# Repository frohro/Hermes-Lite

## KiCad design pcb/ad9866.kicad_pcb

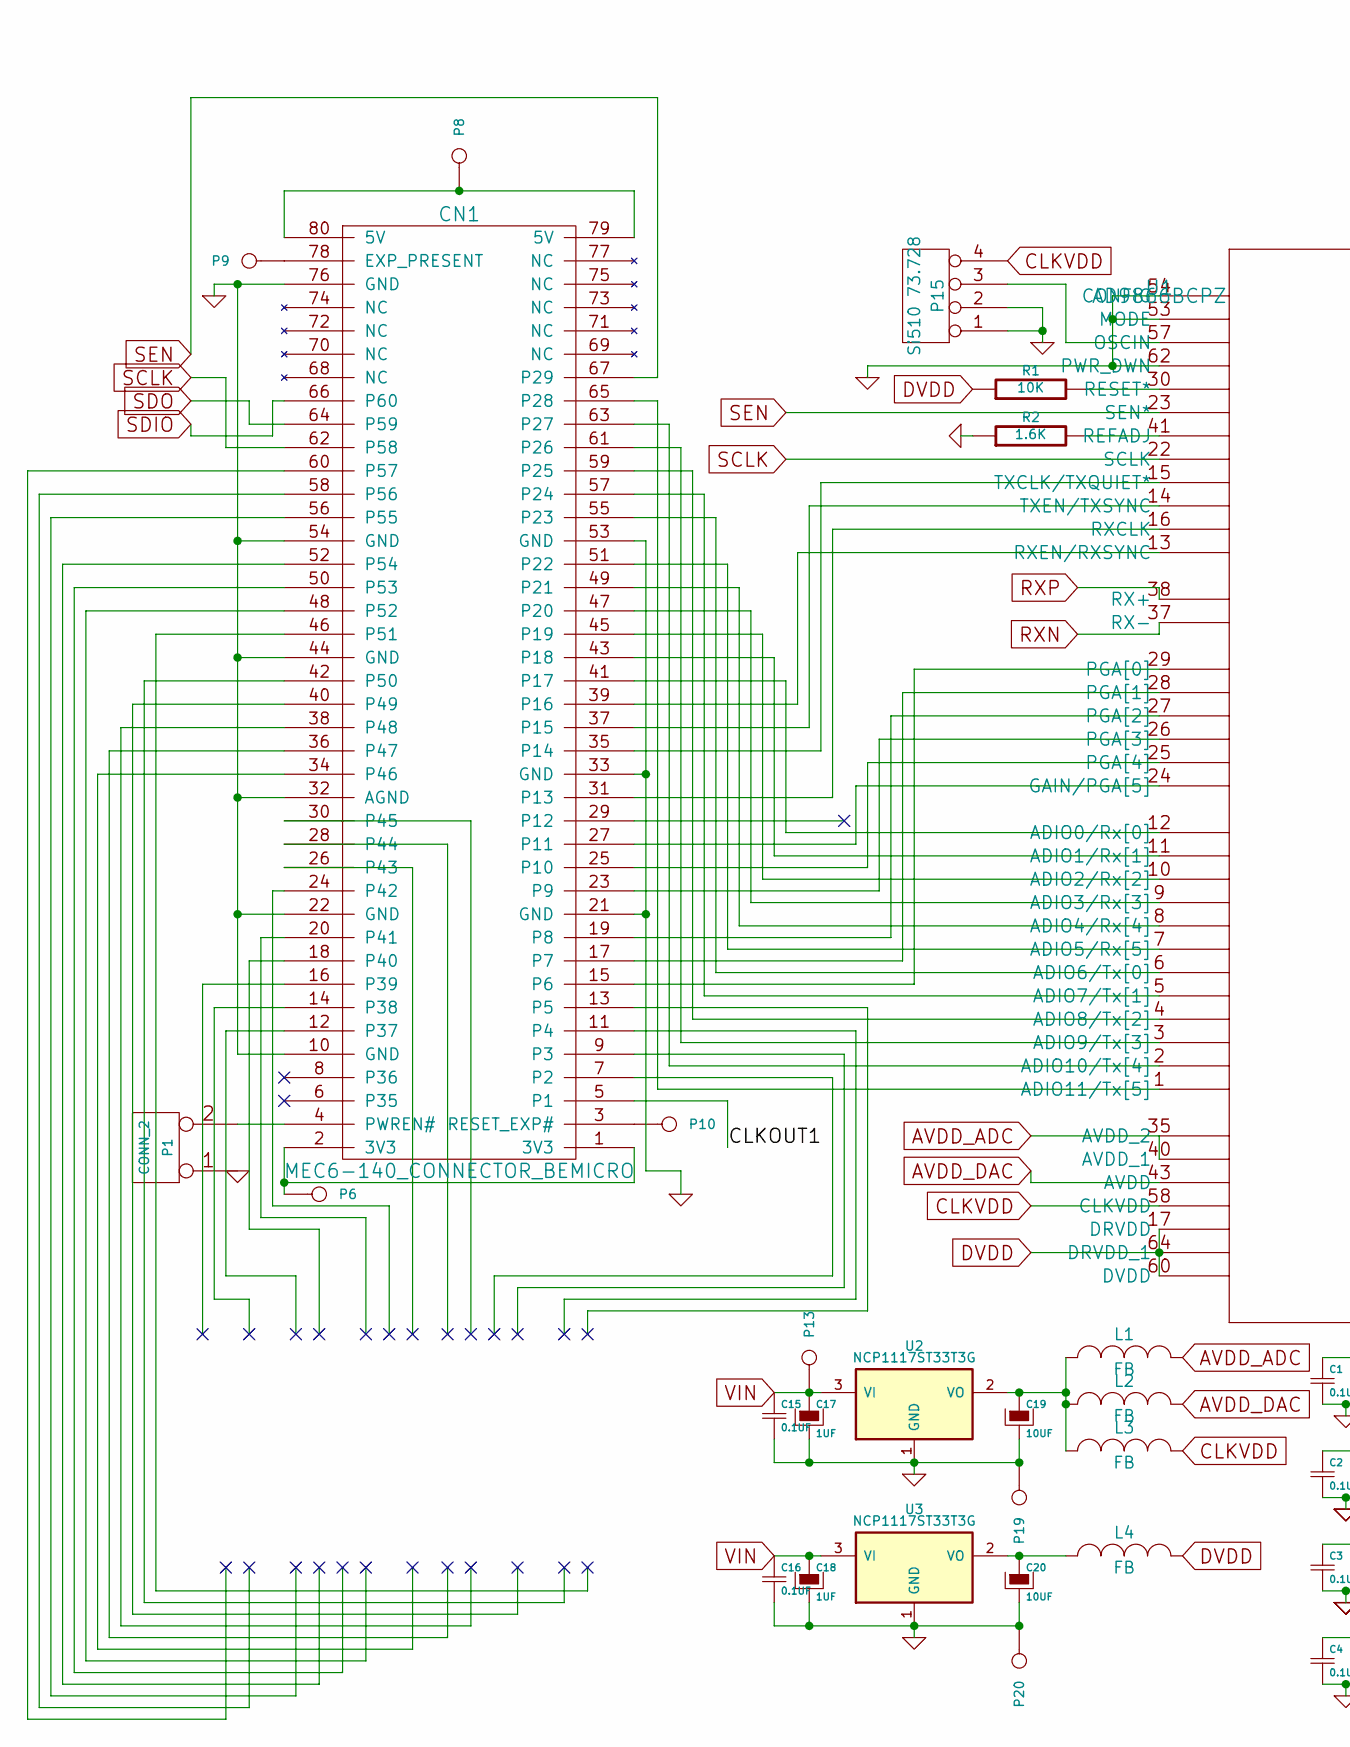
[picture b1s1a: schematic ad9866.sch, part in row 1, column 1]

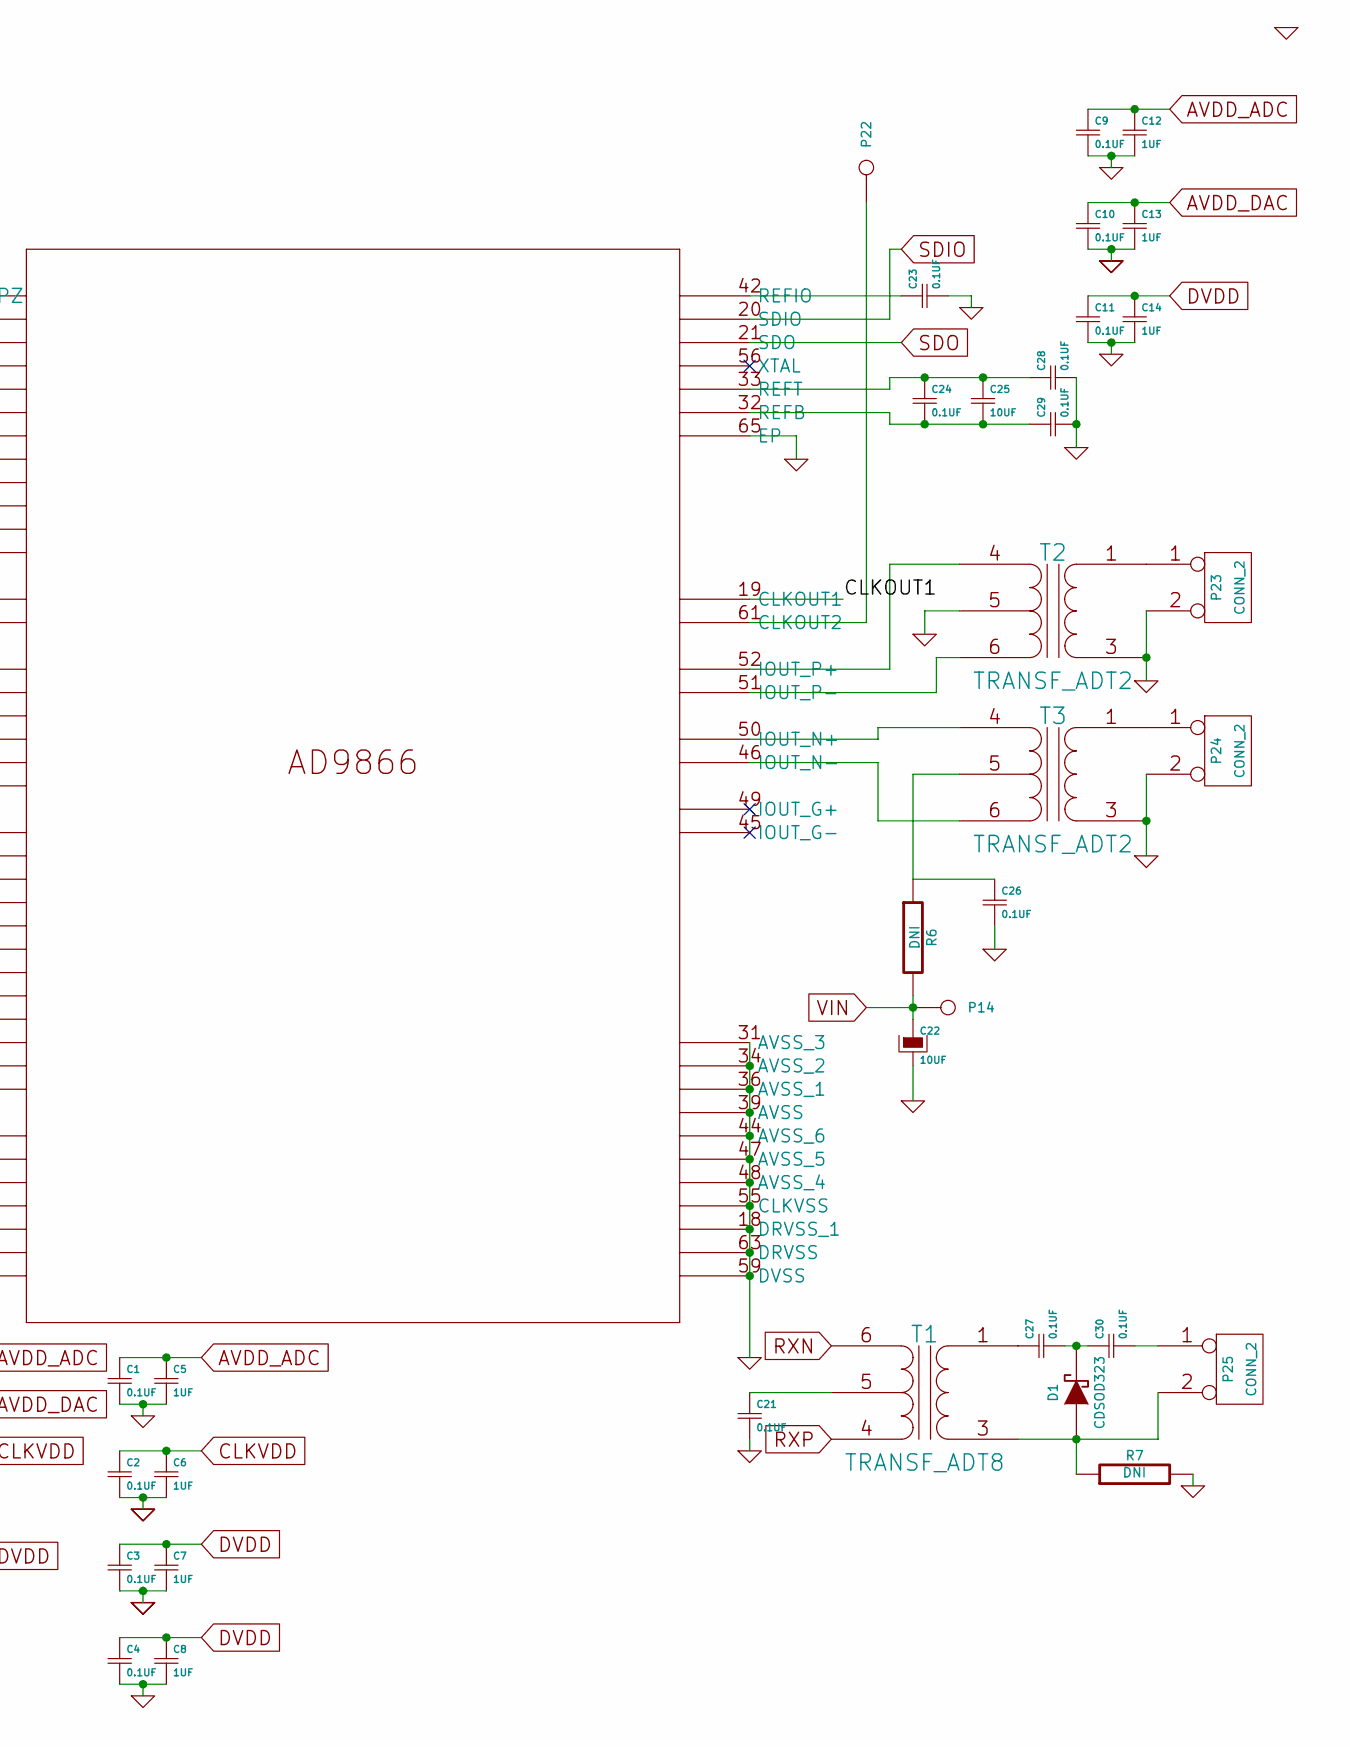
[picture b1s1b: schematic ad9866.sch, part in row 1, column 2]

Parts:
C1, C2, C3, C4, C9, C10, C11, C15, C16, C21, C23, C24, C26, C27, C28, C29, C30: 0.1UF
C5, C6, C7, C8, C12, C13, C14, C17, C18: 1UF
C19, C20, C22, C25: 10UF
CN1: MEC6-140_CONNECTOR_BEMICRO
D1: CDSOD323
L1, L2, L3, L4: FB
P1, P23, P24, P25: CONN_2
P6, P8, P9, P10, P13, P14, P19, P20, P22: CONN_1
P15: Si510 73.728
R1: 10K
R2: 1.6K
R6, R7: DNI
T1: TRANSF_ADT8
T2, T3: TRANSF_ADT2
U1: AD9866BCPZ
U2, U3: NCP1117ST33T3G

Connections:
/CLKOUT1: CN1.5 (P1), U1.19 (CLKOUT1)
AVDD_ADC: C1.1, C5.1, C9.1, C12.1, L1.2, U1.35 (AVDD_2), U1.40 (AVDD_1)
AVDD_DAC: C10.1, C13.1, L2.2, U1.43 (AVDD)
CLKVDD: C2.1, C6.1, L3.2, P15.4, U1.58 (CLKVDD)
DVDD: C3.1, C4.1, C7.1, C8.1, C11.1, C14.1, L4.2, R1.1, U1.17 (DRVDD), U1.60 (DVDD), U1.64 (DRVDD_1)
GND: C1.2, C2.2, C3.2, C4.2, C5.2, C6.2, C7.2, C8.2, C9.2, C10.2, C11.2, C12.2, C13.2, C14.2, C15.2, C16.2, C17.2, C18.2, C19.2, C20.2, C21.2, C22.2, C23.2, C26.2, C28.2, C29.2, CN1.10 (GND), CN1.21 (GND), CN1.22 (GND), CN1.32 (AGND), CN1.33 (GND), CN1.44 (GND), CN1.53 (GND), CN1.54 (GND), CN1.76 (GND), P1.1, P15.1, P15.2, P19.1, P20.1, P23.2 (PM), P24.2 (PM), R2.1, R7.2, T2.3 (S1), T2.5 (PM), T3.3 (S1), U1.18 (DRVSS_1), U1.31 (AVSS_3), U1.34 (AVSS_2), U1.36 (AVSS_1), U1.39 (AVSS), U1.44 (AVSS_6), U1.47 (AVSS_5), U1.48 (AVSS_4), U1.53 (MODE), U1.54 (CONFIG), U1.55 (CLKVSS), U1.59 (DVSS), U1.62 (PWR_DWN), U1.63 (DRVSS), U1.65 (EP), U2.1 (GND), U3.1 (GND)
unnamed: C19.1, L1.1, L2.1, L3.1, U2.2 (VO)
unnamed: C20.1, L4.1, U3.2 (VO)
unnamed: C21.1, T1.5 (PM)
unnamed: C23.1, U1.42 (REFIO)
unnamed: C24.1, C25.1, C28.1, U1.33 (REFT)
unnamed: C24.2, C25.2, C29.1, U1.32 (REFB)
unnamed: C26.1, R6.1, T3.5 (PM)
unnamed: C27.1, T1.1 (S2)
unnamed: C27.2, C30.1, D1.2 (K)
unnamed: C30.2, P25.1
unnamed: CN1.1 (3V3), CN1.2 (3V3), P6.1
unnamed: CN1.3 (RESET_EXP#), P10.1
unnamed: CN1.4 (PWREN#), P1.2 (PM)
unnamed: CN1.15 (P6), U1.29 (PGA[0])
unnamed: CN1.17 (P7), U1.28 (PGA[1])
unnamed: CN1.19 (P8), U1.27 (PGA[2])
unnamed: CN1.23 (P9), U1.26 (PGA[3])
unnamed: CN1.25 (P10), U1.25 (PGA[4])
unnamed: CN1.27 (P11), U1.24 (GAIN/PGA[5])
unnamed: CN1.31 (P13), U1.16 (RXCLK)
unnamed: CN1.35 (P14), U1.15 (TXCLK/TXQUIET*)
unnamed: CN1.37 (P15), U1.14 (TXEN/TXSYNC)
unnamed: CN1.39 (P16), U1.13 (RXEN/RXSYNC)
unnamed: CN1.41 (P17), U1.12 (ADIO0/Rx[0])
unnamed: CN1.43 (P18), U1.11 (ADIO1/Rx[1])
unnamed: CN1.45 (P19), U1.10 (ADIO2/Rx[2])
unnamed: CN1.47 (P20), U1.9 (ADIO3/Rx[3])
unnamed: CN1.49 (P21), U1.8 (ADIO4/Rx[4])
unnamed: CN1.51 (P22), U1.7 (ADIO5/Rx[5])
unnamed: CN1.55 (P23), U1.6 (ADIO6/Tx[0])
unnamed: CN1.57 (P24), U1.5 (ADIO7/Tx[1])
unnamed: CN1.59 (P25), U1.4 (ADIO8/Tx[2])
unnamed: CN1.61 (P26), U1.3 (ADIO9/Tx[3])
unnamed: CN1.63 (P27), U1.2 (ADIO10/Tx[4])
unnamed: CN1.65 (P28), U1.1 (ADIO11/Tx[5])
unnamed: CN1.78 (EXP_PRESENT), P9.1
unnamed: CN1.79 (5V), CN1.80 (5V), P8.1
unnamed: D1.1 (A), P25.2 (PM), R7.1, T1.3 (S1)
unnamed: P15.3, U1.57 (OSCIN)
unnamed: P22.1, U1.61 (CLKOUT2)
unnamed: P23.1, T2.1 (S2)
unnamed: P24.1, T3.1 (S2)
unnamed: R1.2, U1.30 (RESET*)
unnamed: R2.2, U1.41 (REFADJ)
unnamed: T2.4 (PR1), U1.52 (IOUT_P+)
unnamed: T2.6 (PR2), U1.51 (IOUT_P-)
unnamed: T3.4 (PR1), U1.50 (IOUT_N+)
unnamed: T3.6 (PR2), U1.46 (IOUT_N-)
RXN: T1.6 (PR1), U1.37 (RX-)
RXP: T1.4 (PR2), U1.38 (RX+)
SCLK: CN1.62 (P58), U1.22 (SCLK)
SDIO: CN1.66 (P60), U1.20 (SDIO)
SDO: CN1.64 (P59), U1.21 (SDO)
SEN: CN1.67 (P29), U1.23 (SEN*)
VIN: C15.1, C16.1, C17.1, C18.1, C22.1, P13.1, P14.1, R6.2, U2.3 (VI), U3.3 (VI)

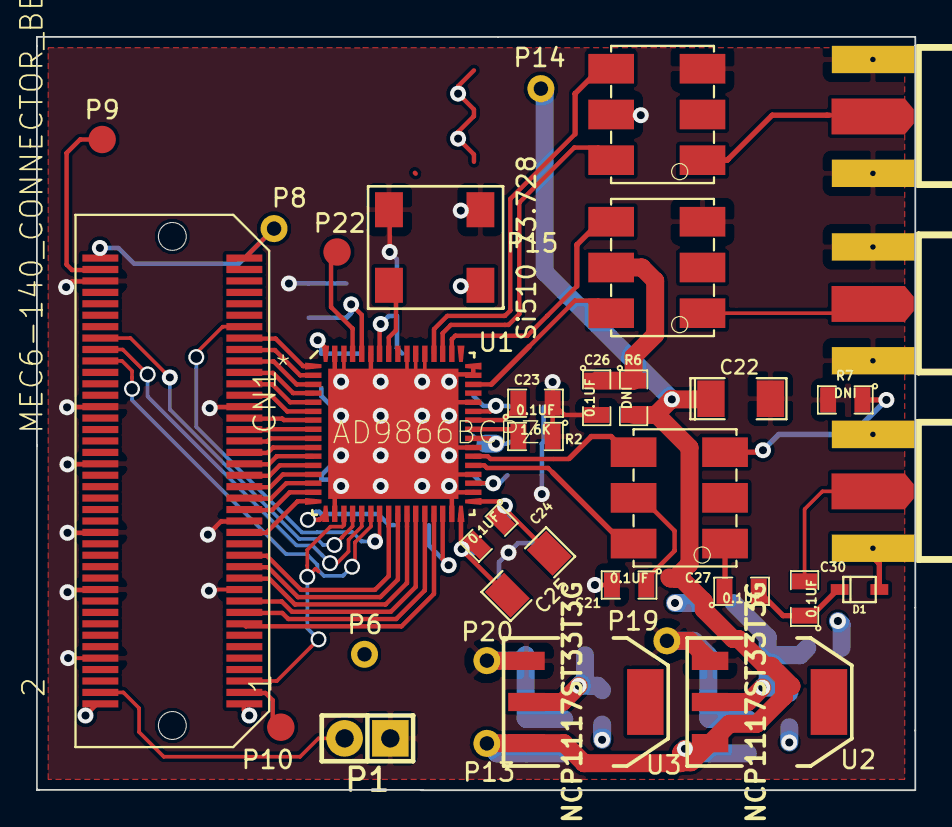
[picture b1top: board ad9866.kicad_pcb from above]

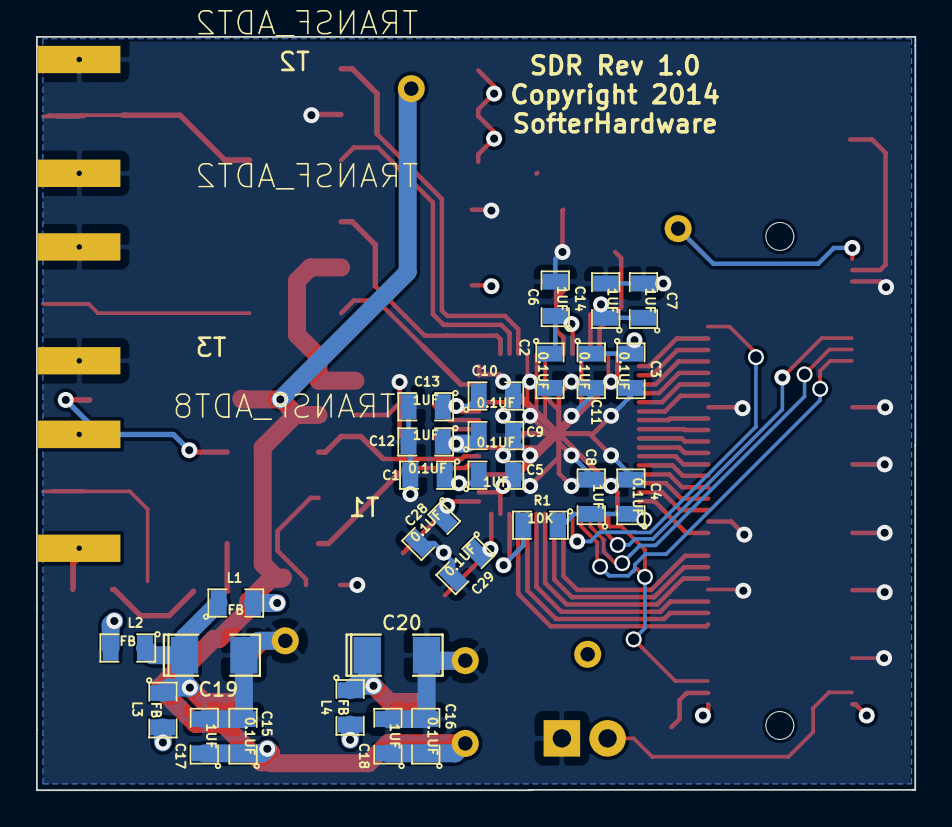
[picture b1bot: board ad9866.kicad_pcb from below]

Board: 4 copper layers, 48.8 x 41.8 mm, 60 parts (27 on the bottom side), 61 nets.

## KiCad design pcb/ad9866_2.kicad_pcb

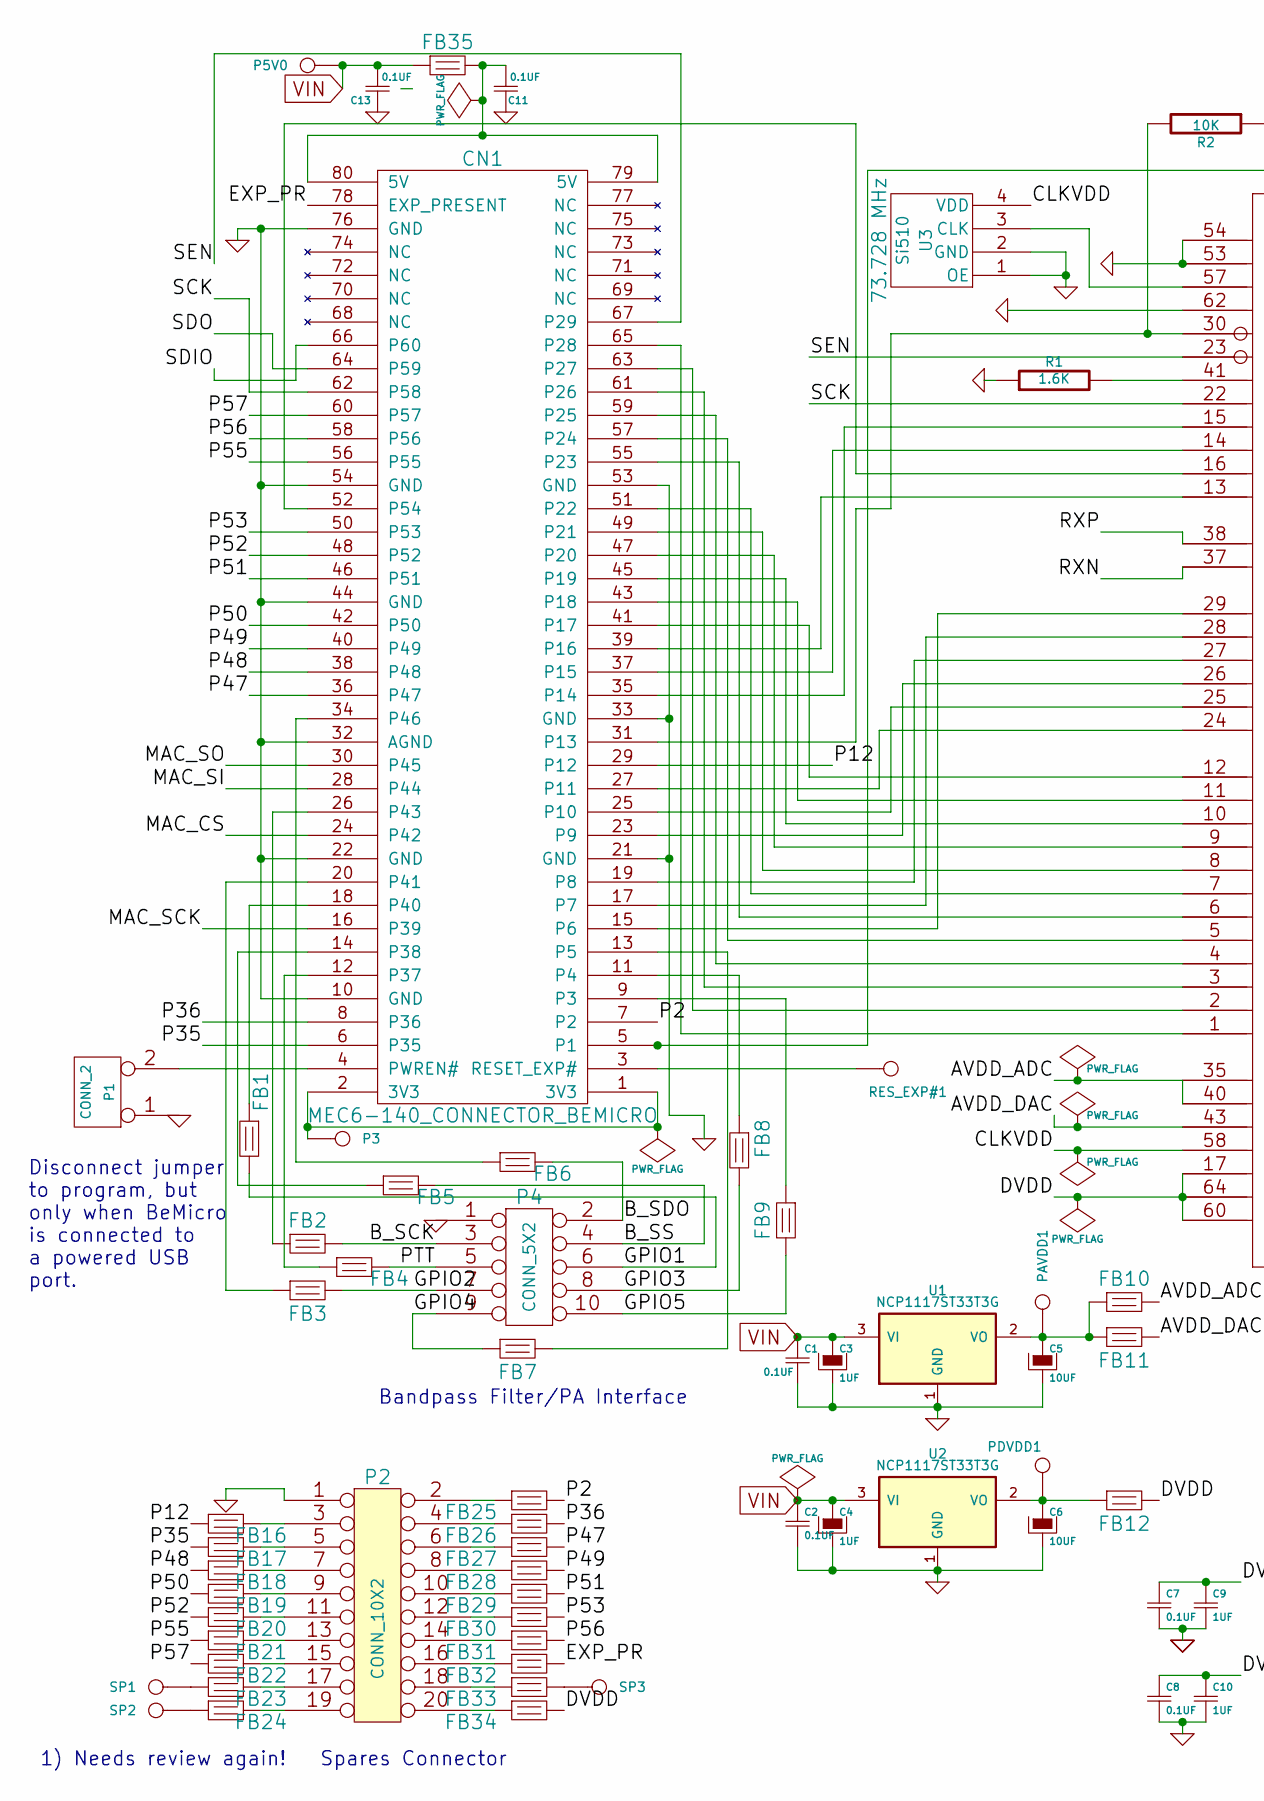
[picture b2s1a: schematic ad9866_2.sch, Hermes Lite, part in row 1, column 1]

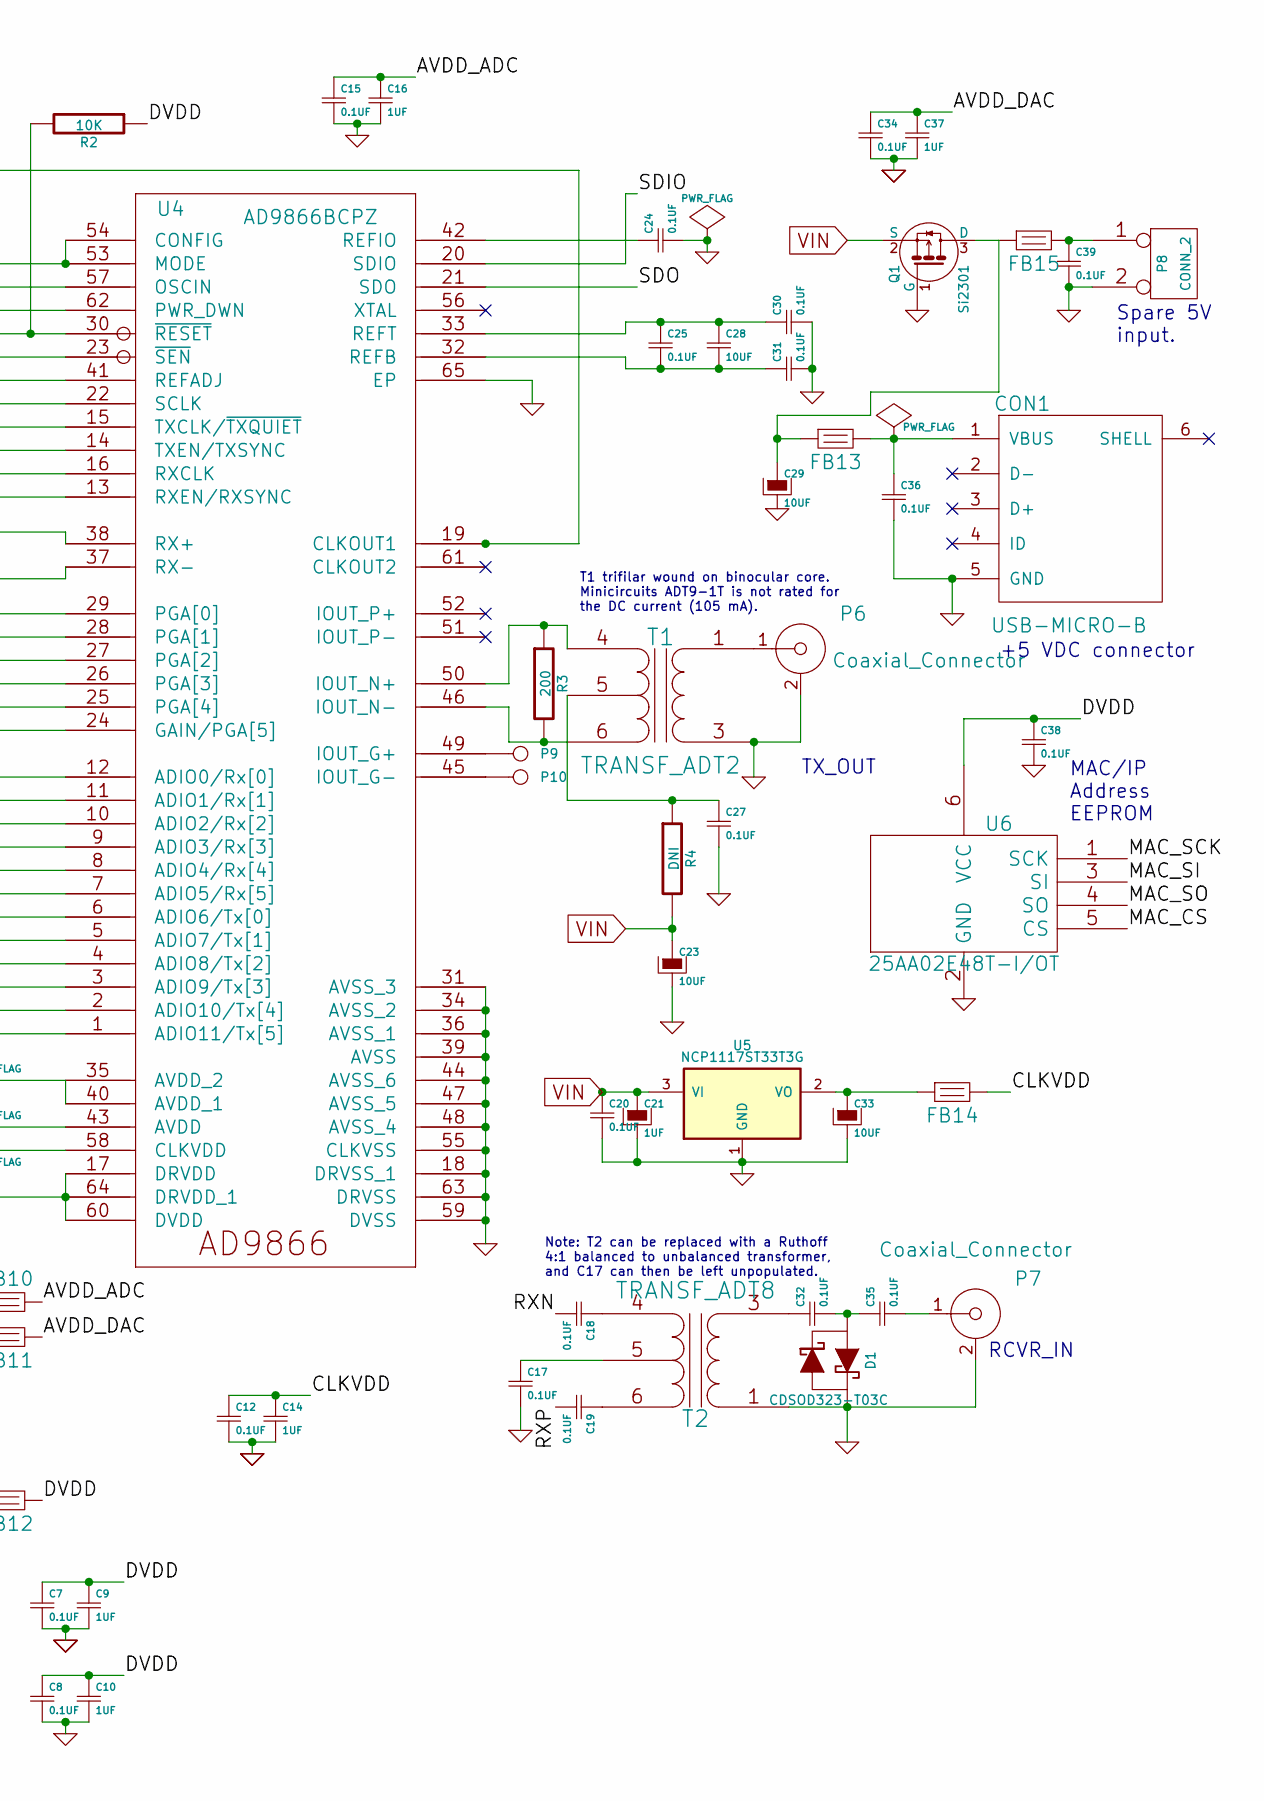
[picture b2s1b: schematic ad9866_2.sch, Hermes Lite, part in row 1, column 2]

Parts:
C1, C2, C7, C8, C11, C12, C13, C15, C17, C18, C19, C20, C24, C25, C27, C30, C31, C32, C34, C35, C36, C38, C39: 0.1UF
C3, C4, C9, C10, C14, C16, C21, C37: 1UF
C5, C6, C23, C28, C29, C33: 10UF
CN1: MEC6-140_CONNECTOR_BEMICRO
CON1: USB-MICRO-B
D1: CDSOD323-T03C
FB1, FB2, FB3, FB4, FB5, FB6, FB7, FB8, FB9, FB10, FB11, FB12, FB13, FB14, FB15, FB16, FB17, FB18, FB19, FB20, FB21, FB22, FB23, FB24, FB25, FB26, FB27, FB28, FB29, FB30, FB31, FB32, FB33, FB34, FB35: FB
P1, P8: CONN_2
P2: CONN_10X2
P3, P5V0, P9, P10: CONN_1
P4: CONN_5X2
P6, P7: Coaxial_Connector
PAVDD1: CONN_1
PDVDD1: CONN_1
Q1: Si2301; SOT-23
R1: 1.6K
R2: 10K
R3: 200
R4: DNI
RES_EXP#1: CONN_1
SP1, SP2, SP3: CONN_1
T1: TRANSF_ADT2
T2: TRANSF_ADT8
U1, U2, U5: NCP1117ST33T3G
U3: Si510
U4: AD9866BCPZ
U6: 25AA02E48T-I/OT

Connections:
/B_SCK: FB2.2, P4.3
/B_SDO: FB6.2, P4.2
/B_SS: FB5.2, P4.4
/EXP_PR: CN1.78 (EXP_PRESENT), FB32.2
/GPIO1: FB1.2, P4.6
/GPIO2: FB3.2, P4.7
/GPIO3: FB8.2, P4.8
/GPIO4: FB7.1, P4.9
/GPIO5: FB9.2, P4.10
/MAC_CS: CN1.24 (P42), U6.5 (CS)
/MAC_SCK: CN1.16 (P39), U6.1 (SCK)
/MAC_SI: CN1.28 (P44), U6.3 (SI)
/MAC_SO: CN1.30 (P45), U6.4 (SO)
/P2: CN1.7 (P2), FB25.2
/P12: CN1.29 (P12), FB16.1
/P35: CN1.6 (P35), FB17.1
/P36: CN1.8 (P36), FB26.2
/P47: CN1.36 (P47), FB27.2
/P48: CN1.38 (P48), FB18.1
/P49: CN1.40 (P49), FB28.2
/P50: CN1.42 (P50), FB19.1
/P51: CN1.46 (P51), FB29.2
/P52: CN1.48 (P52), FB20.1
/P53: CN1.50 (P53), FB30.2
/P55: CN1.56 (P55), FB21.1
/P56: CN1.58 (P56), FB31.2
/P57: CN1.60 (P57), FB22.1
/PTT: FB4.2, P4.5
/RXN: C18.2, U4.37 (RX-)
/RXP: C19.2, U4.38 (RX+)
/SCK: CN1.62 (P58), U4.22 (SCLK)
/SDIO: CN1.66 (P60), U4.20 (SDIO)
/SDO: CN1.64 (P59), U4.21 (SDO)
/SEN: CN1.67 (P29), U4.23 (~SEN)
GND: C1.2, C2.2, C3.2, C4.2, C5.2, C6.2, C7.2, C8.2, C9.2, C10.2, C11.1, C12.2, C13.1, C14.2, C15.2, C16.2, C17.2, C20.2, C21.2, C23.2, C24.2, C27.2, C29.2, C30.2, C31.2, C33.2, C34.2, C36.2, C37.2, C38.2, C39.2, CN1.10 (GND), CN1.21 (GND), CN1.22 (GND), CN1.32 (AGND), CN1.33 (GND), CN1.44 (GND), CN1.53 (GND), CN1.54 (GND), CN1.76 (GND), CON1.5 (GND), D1.2 (K), P1.1, P2.1, P4.1, P6.2 (Shield), P7.2 (Shield), P8.2 (PM), Q1.1 (G), R1.1, T1.3 (S1), T2.1 (S2), U1.1 (GND), U2.1 (GND), U3.1 (OE), U3.2 (GND), U4.18 (DRVSS_1), U4.31 (AVSS_3), U4.34 (AVSS_2), U4.36 (AVSS_1), U4.39 (AVSS), U4.44 (AVSS_6), U4.47 (AVSS_5), U4.48 (AVSS_4), U4.53 (MODE), U4.54 (CONFIG), U4.55 (CLKVSS), U4.59 (DVSS), U4.62 (PWR_DWN), U4.63 (DRVSS), U4.65 (EP), U5.1 (GND), U6.2 (GND); also elsewhere on the board
unnamed: C5.1, FB10.1, FB11.1, PAVDD1.1, U1.2 (VO)
unnamed: C6.1, FB12.1, PDVDD1.1, U2.2 (VO)
unnamed: C11.2, CN1.79 (5V), CN1.80 (5V), FB35.2
unnamed: C17.1, T2.5 (PM)
unnamed: C18.1, T2.4 (PR2)
unnamed: C19.1, T2.6 (PR1)
unnamed: C24.1, U4.42 (REFIO)
unnamed: C25.1, C28.1, C30.1, U4.33 (REFT)
unnamed: C25.2, C28.2, C31.1, U4.32 (REFB)
unnamed: C27.1, R4.1, T1.5 (PM)
unnamed: C29.1, FB13.1, FB15.1, Q1.3 (D)
unnamed: C32.1, T2.3 (S1)
unnamed: C32.2, C35.1, D1.1 (A)
unnamed: C33.1, FB14.1, U5.2 (VO)
unnamed: C35.2, P7.1 (Center_Conductor)
unnamed: C36.1, CON1.1 (VBUS), FB13.2
unnamed: C39.1, FB15.2, P8.1
unnamed: CN1.1 (3V3), CN1.2 (3V3), P3.1
unnamed: CN1.3 (RESET_EXP#), RES_EXP#1.1
unnamed: CN1.4 (PWREN#), P1.2 (PM)
unnamed: CN1.5 (P1), U4.19 (CLKOUT1)
unnamed: CN1.9 (P3), FB9.1
unnamed: CN1.11 (P4), FB8.1
unnamed: CN1.12 (P37), FB4.1
unnamed: CN1.13 (P5), FB7.2
unnamed: CN1.14 (P38), FB5.1
unnamed: CN1.15 (P6), U4.29 (PGA[0])
unnamed: CN1.17 (P7), U4.28 (PGA[1])
unnamed: CN1.18 (P40), FB1.1
unnamed: CN1.19 (P8), U4.27 (PGA[2])
unnamed: CN1.20 (P41), FB3.1
unnamed: CN1.23 (P9), U4.26 (PGA[3])
unnamed: CN1.25 (P10), U4.25 (PGA[4])
unnamed: CN1.26 (P43), FB2.1
unnamed: CN1.27 (P11), U4.24 (GAIN/PGA[5])
unnamed: CN1.31 (P13), R2.2, U4.30 (~RESET)
unnamed: CN1.34 (P46), FB6.1
unnamed: CN1.35 (P14), U4.15 (TXCLK/~TXQUIET)
unnamed: CN1.37 (P15), U4.14 (TXEN/TXSYNC)
unnamed: CN1.39 (P16), U4.13 (RXEN/RXSYNC)
unnamed: CN1.41 (P17), U4.12 (ADIO0/Rx[0])
unnamed: CN1.43 (P18), U4.11 (ADIO1/Rx[1])
unnamed: CN1.45 (P19), U4.10 (ADIO2/Rx[2])
unnamed: CN1.47 (P20), U4.9 (ADIO3/Rx[3])
unnamed: CN1.49 (P21), U4.8 (ADIO4/Rx[4])
unnamed: CN1.51 (P22), U4.7 (ADIO5/Rx[5])
unnamed: CN1.52 (P54), U4.16 (RXCLK)
unnamed: CN1.55 (P23), U4.6 (ADIO6/Tx[0])
unnamed: CN1.57 (P24), U4.5 (ADIO7/Tx[1])
unnamed: CN1.59 (P25), U4.4 (ADIO8/Tx[2])
unnamed: CN1.61 (P26), U4.3 (ADIO9/Tx[3])
unnamed: CN1.63 (P27), U4.2 (ADIO10/Tx[4])
unnamed: CN1.65 (P28), U4.1 (ADIO11/Tx[5])
unnamed: FB16.2, P2.3
unnamed: FB17.2, P2.5
unnamed: FB18.2, P2.7
unnamed: FB19.2, P2.9
unnamed: FB20.2, P2.11
unnamed: FB21.2, P2.13
unnamed: FB22.2, P2.15
unnamed: FB23.1, SP1.1
unnamed: FB23.2, P2.17
unnamed: FB24.1, SP2.1
unnamed: FB24.2, P2.19
unnamed: FB25.1, P2.2
unnamed: FB26.1, P2.4
unnamed: FB27.1, P2.6
unnamed: FB28.1, P2.8
unnamed: FB29.1, P2.10
unnamed: FB30.1, P2.12
unnamed: FB31.1, P2.14
unnamed: FB32.1, P2.16
unnamed: FB33.1, P2.18
unnamed: FB33.2, SP3.1
unnamed: FB34.1, P2.20
unnamed: P6.1 (Center_Conductor), T1.1 (S2)
unnamed: P9.1, U4.49 (IOUT_G+)
unnamed: P10.1, U4.45 (IOUT_G-)
unnamed: R1.2, U4.41 (REFADJ)
unnamed: R3.1, T1.4 (PR1), U4.50 (IOUT_N+)
unnamed: R3.2, T1.6 (PR2), U4.46 (IOUT_N-)
unnamed: U3.3 (CLK), U4.57 (OSCIN)
VIN: C1.1, C2.1, C3.1, C4.1, C13.2, C20.1, C21.1, C23.1, FB35.1, P5V0.1, Q1.2 (S), R4.2, U1.3 (VI), U2.3 (VI), U5.3 (VI)

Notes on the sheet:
Bandpass Filter/PA Interface
RCVR_IN
TX_OUT
Disconnect jumper to program, but only when BeMicro is connected to a powered USB port.
+5 VDC connector
MAC/IP Address EEPROM
1) Needs review again!
Spare 5V input.
Note: T2 can be replaced with a Ruthoff 4:1 balanced to unbalanced transformer, and C17 can then be left unpopulated.
T1 trifilar wound on binocular core. Minicircuits ADT9-1T is not rated for the DC current (105 mA).
Spares Connector

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
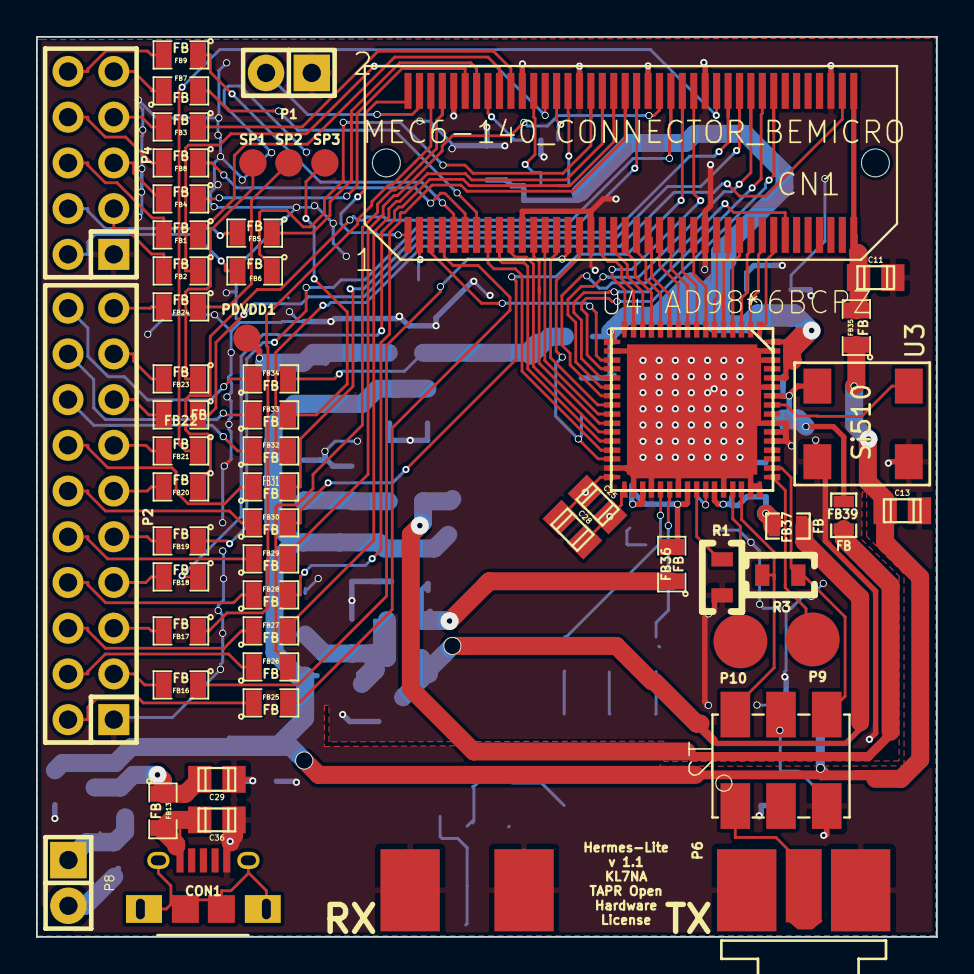
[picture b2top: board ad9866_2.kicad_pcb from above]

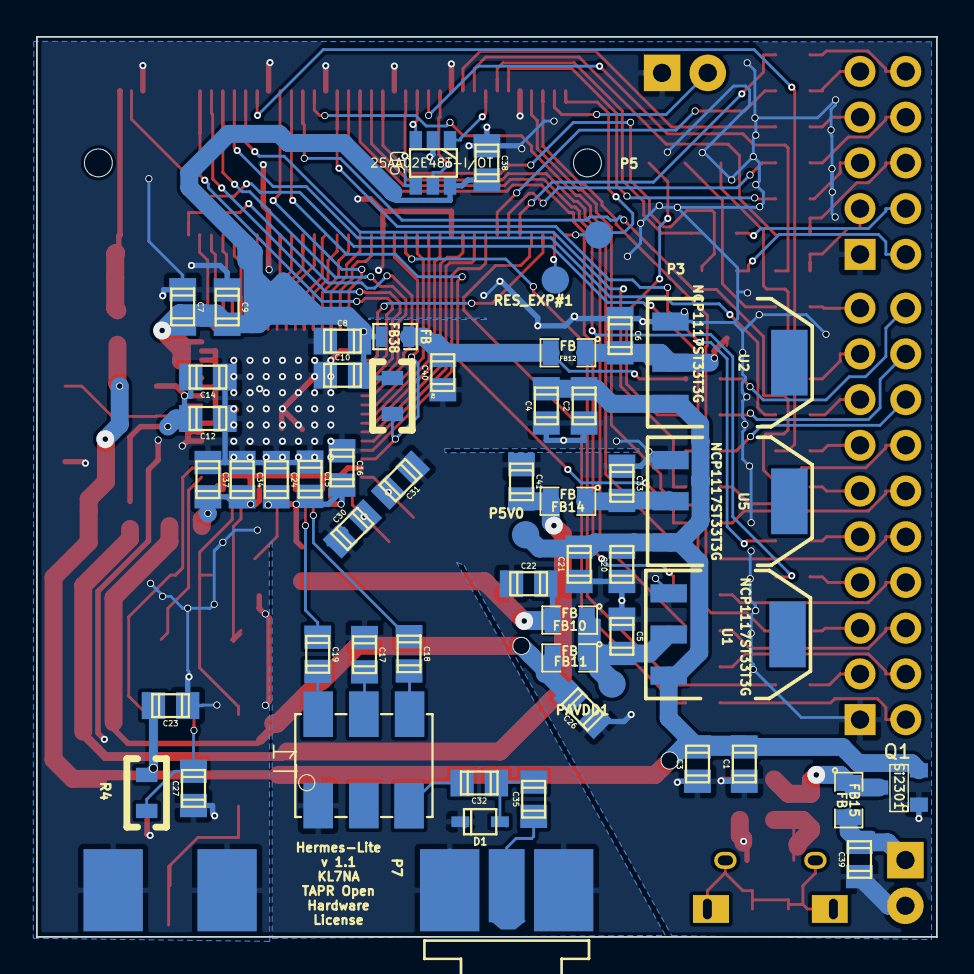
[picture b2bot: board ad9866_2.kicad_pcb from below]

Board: 4 copper layers, 50.0 x 50.0 mm, 113 parts (56 on the bottom side), 126 nets.

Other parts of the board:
C22, C26, C40, C41: 0.1UF; c_0805
FB36: FB; SM0805
FB37, FB38, FB39: FB; SM0603_Resistor
P5: CONN_1; Measurement_Point_Round-SMD-Pad_Small

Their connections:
GND: C22.2, C26.2, C40.2, C41.2; also elsewhere on the board

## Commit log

2014-06-16 Initial v-1.1 commit
2014-06-16 adding libraries needed
2014-06-17 ground plane revisions
2014-06-19 Revised after first review.
2014-06-19 Added a slit to separate DVDD and AVDD_ADC, and provisions for shield.
2014-06-20 Added all the libs dir.
2014-06-20 Fixed the ADC reference caps.
2014-06-20 Added doc link for ferrite beads.
2014-06-20 Added more FB's and bypass caps.
2014-06-20 Added thermal relief.
2014-06-20 Special attention to the routing of CLKOUT1.
2014-06-20 Special attention to the routing of CLKOUT1, added cutout & filled.
2014-06-20 Special attention to the routing of CLKOUT1, added more ground plane.
2014-06-20 Removed a few 90 degree corners, cleaned up a few traces.
2014-06-21 Removed the solder mask to make installing copper tape shields.
2014-06-22 Routed the CLKOUT on only front side, but made a lot of vias on other signals.
2014-06-22 Probably abandoning this branch....
2014-06-22 Made power traces much wider where possible.
2014-06-23 Filled in ground plane where I could, and made DRC work again.
2014-06-23 Filled in a few more places on the ground plane.
2014-06-25 Deleted a via way out in right field. Still passes DRC.
2014-06-25 New Gerbers.
2014-06-25 Changed schematic and .cmp for issues 12 & 16-20
2014-06-25 Think 12 is fixed; routed by hand all changes.
2014-06-25 Just making sure everything is saved.
2014-06-26 to switch branches
2014-06-26 Changed the SMA to SMA edge connectors, because then they are the same as the other board, and to get around the slight possibility the holes still are not right.
2014-06-26 version submitted.
2014-06-27 Working on BOM...
2014-06-29 Fixed the holes in the SMA Edge connectors to be 0.3 mm.
2014-06-30 Fixed soldermask on P23-25.
2014-06-30 Fixed SMA connectors correctly this time.
2014-06-30 Fixed soldermask missing on SMA edge connectors.
2014-07-11 Cosmetic fixes to schematic.
2014-07-13 Added rudimentary BOM for v-1.1
2014-07-15 Added the bottom ground plane in.

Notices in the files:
pcb/ad9866.kicad_pcb:
Copyright 2014
